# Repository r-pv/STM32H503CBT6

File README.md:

# STM32H503CBT6
ST development board based on the STM32H503CBT6 MCU. Compatible with Arduino.

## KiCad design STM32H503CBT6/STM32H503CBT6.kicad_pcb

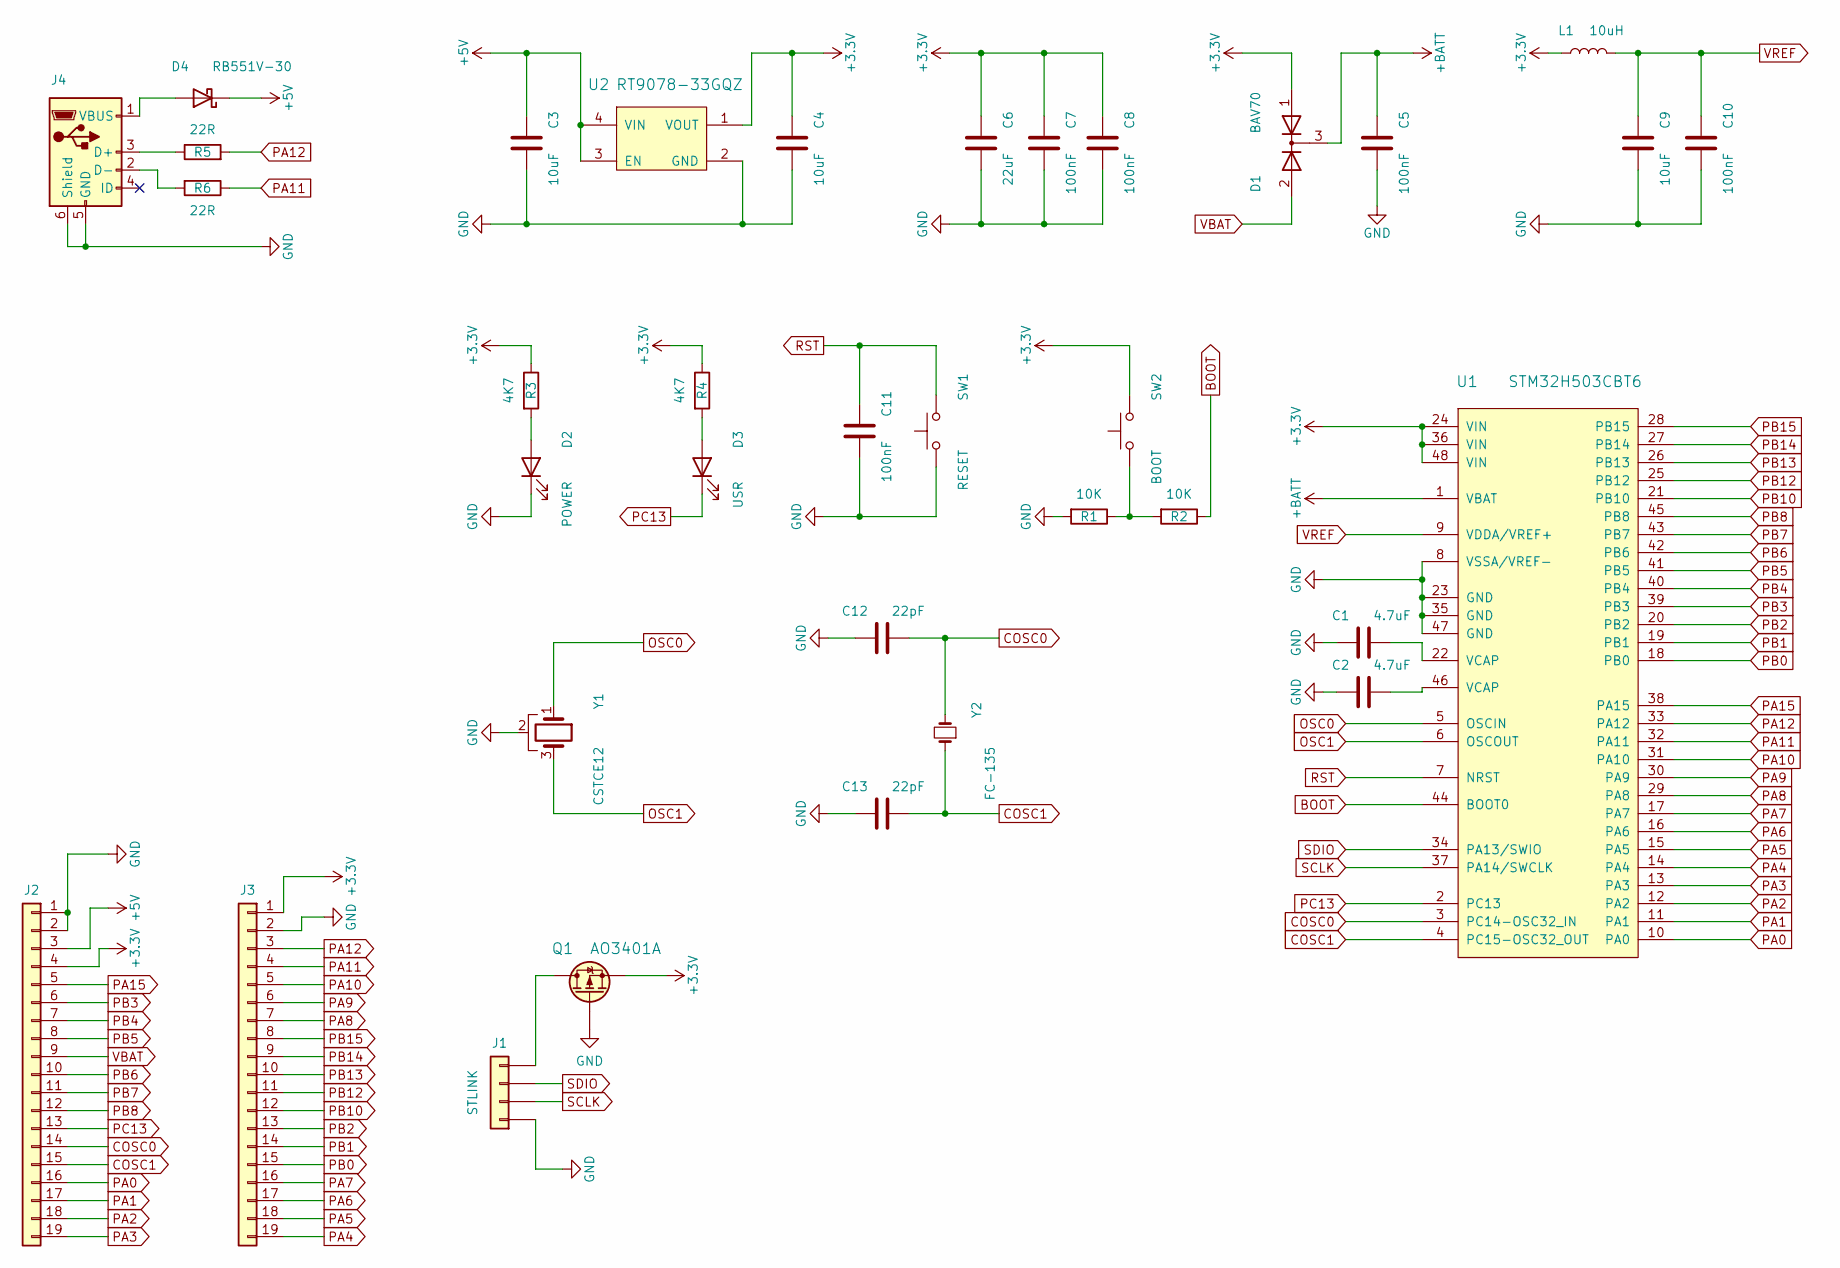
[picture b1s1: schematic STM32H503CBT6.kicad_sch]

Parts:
C1, C2: 4.7uF; C_0402_1005Metric
C3, C4, C9: 10uF; C_0402_1005Metric
C5, C7, C8, C10, C11: 100nF; C_0402_1005Metric
C6: 22uF; C_0805_2012Metric
C12, C13: 22pF; C_0402_1005Metric
D1: BAV70; SOT-23
D2: POWER; LED_0603_1608Metric
D3: USR; LED_0603_1608Metric
D4: RB551V-30; D_SOD-323
J1: STLINK; PinSocket_1x04_P2.54mm_Vertical
J2, J3: PinSocket_1x19_P2.54mm_Vertical
J4: connector_USB_Micro-B2
L1: 10uH; L_0603_1608Metric
Q1: AO3401A; SOT-23
R1, R2: 10K; R_0402_1005Metric
R3, R4: 4K7; R_0402_1005Metric
R5, R6: 22R; R_0402_1005Metric
SW1: RESET; Switch_SMD_5.2x6.4_reset
SW2: BOOT; Switch_SMD_5.2x6.4_reset
U1: STM32H503CBT6; LQFP-48_7x7mm_P0.5mm
U2: RT9078-33GQZ; XDFN4_1x1mm_0.65P
Y1: CSTCE12; Crystal_CSTCE_3pin_3.2x1.3
Y2: FC-135; Crystal_FC-135

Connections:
+3.3V: C4.1, C6.1, C7.1, C8.1, D1.1 (A), J2.4, J3.1, L1.1, Q1.2 (S), R3.1, R4.1, SW2.2, U1.24 (VIN), U1.36 (VIN), U1.48 (VIN), U2.1 (VOUT)
+5V: C3.1, D4.1 (K), J2.3, U2.3 (EN), U2.4 (VIN)
+BATT: C5.1, D1.3 (K), U1.1 (VBAT)
BOOT: R2.1, U1.44 (BOOT0)
COSC0: C12.2, J2.14, U1.3 (PC14-OSC32_IN), Y2.2
COSC1: C13.2, J2.15, U1.4 (PC15-OSC32_OUT), Y2.1
GND: C1.1, C2.1, C3.2, C4.2, C5.2, C6.2, C7.2, C8.2, C9.2, C10.2, C11.2, C12.1, C13.1, D2.1 (K), J1.1, J2.1, J2.2, J3.2, J4.5 (GND), J4.6 (Shield), Q1.1 (G), R1.2, SW1.1, U1.8 (VSSA/VREF-), U1.23 (GND), U1.35 (GND), U1.47 (GND), U2.2 (GND), Y1.2
unnamed: C1.2, U1.22 (VCAP)
unnamed: C2.2, U1.46 (VCAP)
unnamed: D2.2 (A), R3.2
unnamed: D3.2 (A), R4.2
unnamed: D4.2 (A), J4.1 (VBUS)
unnamed: J1.4, Q1.3 (D)
unnamed: J4.3 (D+), R5.1
unnamed: J4.2 (D-), R6.2
unnamed: R1.1, R2.2, SW2.1
OSC0: U1.5 (OSCIN), Y1.1
OSC1: U1.6 (OSCOUT), Y1.3
PA0: J2.16, U1.10 (PA0)
PA1: J2.17, U1.11 (PA1)
PA2: J2.18, U1.12 (PA2)
PA3: J2.19, U1.13 (PA3)
PA4: J3.19, U1.14 (PA4)
PA5: J3.18, U1.15 (PA5)
PA6: J3.17, U1.16 (PA6)
PA7: J3.16, U1.17 (PA7)
PA8: J3.7, U1.29 (PA8)
PA9: J3.6, U1.30 (PA9)
PA10: J3.5, U1.31 (PA10)
PA11: J3.4, R6.1, U1.32 (PA11)
PA12: J3.3, R5.2, U1.33 (PA12)
PA15: J2.5, U1.38 (PA15)
PB0: J3.15, U1.18 (PB0)
PB1: J3.14, U1.19 (PB1)
PB2: J3.13, U1.20 (PB2)
PB3: J2.6, U1.39 (PB3)
PB4: J2.7, U1.40 (PB4)
PB5: J2.8, U1.41 (PB5)
PB6: J2.10, U1.42 (PB6)
PB7: J2.11, U1.43 (PB7)
PB8: J2.12, U1.45 (PB8)
PB10: J3.12, U1.21 (PB10)
PB12: J3.11, U1.25 (PB12)
PB13: J3.10, U1.26 (PB13)
PB14: J3.9, U1.27 (PB14)
PB15: J3.8, U1.28 (PB15)
PC13: D3.1 (K), J2.13, U1.2 (PC13)
RST: C11.1, SW1.2, U1.7 (NRST)
SCLK: J1.2, U1.37 (PA14/SWCLK)
SDIO: J1.3, U1.34 (PA13/SWIO)
VBAT: D1.2 (A), J2.9
VREF: C9.1, C10.1, L1.2, U1.9 (VDDA/VREF+)

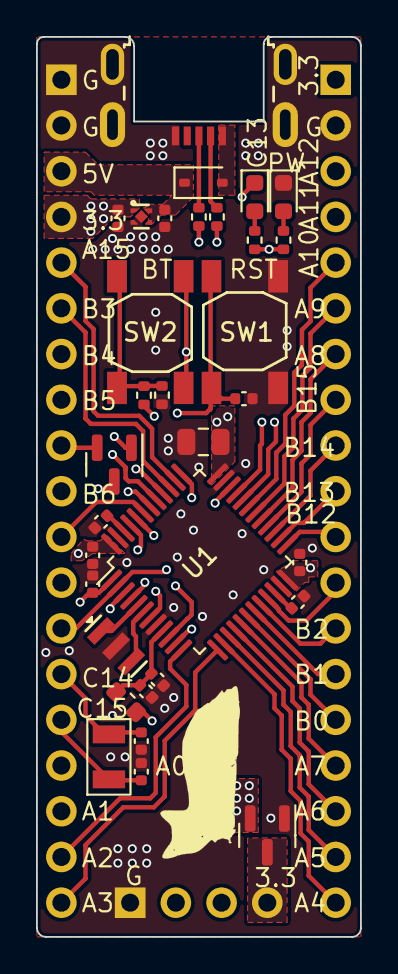
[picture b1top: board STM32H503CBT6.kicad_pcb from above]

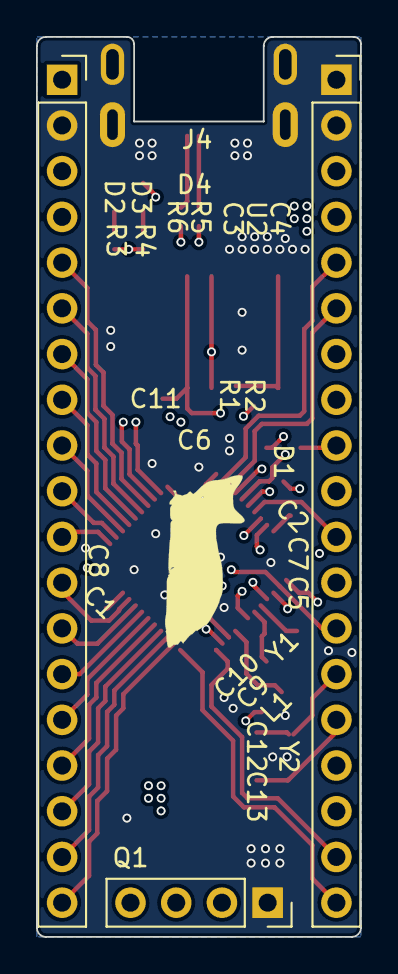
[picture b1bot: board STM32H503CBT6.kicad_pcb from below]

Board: 4 copper layers, 18.0 x 50.0 mm, 35 parts (3 on the bottom side), 52 nets.

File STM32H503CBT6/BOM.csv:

"Reference","Value","Footprint","Datasheet","Qty"
"C1, C2","4.7uF","Capacitor_SMD:C_0402_1005Metric","~","2"
"C3, C4, C9","10uF","Capacitor_SMD:C_0402_1005Metric","~","3"
"C5, C7, C8, C10, C11","100nF","Capacitor_SMD:C_0402_1005Metric","~","5"
"C6","22uF","Capacitor_SMD:C_0805_2012Metric","~","1"
"C12, C13","22pF","Capacitor_SMD:C_0402_1005Metric","~","2"
"D1","BAV70","Package_TO_SOT_SMD:SOT-23","https://assets.nexperia.com/documents/data-sheet/BAV70_SER.pdf","1"
"D2","POWER","LED_SMD:LED_0603_1608Metric","~","1"
"D3","USR","LED_SMD:LED_0603_1608Metric","~","1"
"D4","RB551V-30","Diode_SMD:D_SOD-323","~","1"
"J1","STLINK","Connector_PinSocket_2.54mm:PinSocket_1x04_P2.54mm_Vertical","~","1"
"J2, J3"," ","Connector_PinSocket_2.54mm:PinSocket_1x19_P2.54mm_Vertical","~","2"
"J4"," ","connector_USB_Micro-B2","~","1"
"L1","10uH","Inductor_SMD:L_0603_1608Metric","~","1"
"Q1","AO3401A","Package_TO_SOT_SMD:SOT-23","","1"
"R1, R2","10K","Resistor_SMD:R_0402_1005Metric","~","2"
"R3, R4","4K7","Resistor_SMD:R_0402_1005Metric","~","2"
"R5, R6","22R","Resistor_SMD:R_0402_1005Metric","~","2"
"SW1","RESET","Switch_SMD_5.2x6.4_reset","~","1"
"SW2","BOOT","Switch_SMD_5.2x6.4_reset","~","1"
"U1","STM32H503CBT6","Package_QFP:LQFP-48_7x7mm_P0.5mm","","1"
"U2","RT9078-33GQZ","XDFN4_1x1mm_0.65P","","1"
"Y1","CSTCE12","Crystal_CSTCE_3pin_3.2x1.3","~","1"
"Y2","FC-135


","Crystal_FC-135","~","1"

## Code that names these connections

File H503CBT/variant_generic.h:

/*
 *******************************************************************************
 * Copyright (c) 2020, STMicroelectronics
 * All rights reserved.
 *
 * This software component is licensed by ST under BSD 3-Clause license,
 * the "License"; You may not use this file except in compliance with the
 * License. You may obtain a copy of the License at:
 *                        opensource.org/licenses/BSD-3-Clause
 *
 *******************************************************************************
 */
#pragma once

/*----------------------------------------------------------------------------
 *        STM32 pins number
 *----------------------------------------------------------------------------*/
#define PA0                     PIN_A0
#define PA1                     PIN_A1
#define PA2                     PIN_A2
#define PA3                     PIN_A3
#define PA4                     PIN_A4
#define PA5                     PIN_A5
#define PA6                     PIN_A6
#define PA7                     PIN_A7
#define PA8                     8
#define PA9                     9
#define PA10                    10
#define PA11                    11
#define PA12                    12
#define PA13                    13
#define PA14                    14
#define PA15                    15
#define PB0                     PIN_A8
#define PB1                     PIN_A9
#define PB2                     18
#define PB3                     19
#define PB4                     20
#define PB5                     21
#define PB6                     22
#define PB7                     23
#define PB8                     24
#define PB10                    25
#define PB12                    26
#define PB13                    27
#define PB14                    28
#define PB15                    29
#define PC13                    30
#define PC14                    31
#define PC15                    32
#define PH0                     33
#define PH1                     34

// Alternate pins number
#define PA0_ALT1                (PA0  | ALT1)
#define PA0_ALT2                (PA0  | ALT2)
#define PA1_ALT1                (PA1  | ALT1)
#define PA2_ALT1                (PA2  | ALT1)
#define PA3_ALT1                (PA3  | ALT1)
#define PA4_ALT1                (PA4  | ALT1)
#define PA5_ALT1                (PA5  | ALT1)
#define PA7_ALT1                (PA7  | ALT1)
#define PA7_ALT2                (PA7  | ALT2)
#define PA8_ALT1                (PA8  | ALT1)
#define PA8_ALT2                (PA8  | ALT2)
#define PA9_ALT1                (PA9  | ALT1)
#define PA10_ALT1               (PA10 | ALT1)
#define PA11_ALT1               (PA11 | ALT1)
#define PA12_ALT1               (PA12 | ALT1)
#define PA13_ALT1               (PA13 | ALT1)
#define PA14_ALT1               (PA14 | ALT1)
#define PA14_ALT2               (PA14 | ALT2)
#define PA15_ALT1               (PA15 | ALT1)
#define PB0_ALT1                (PB0  | ALT1)
#define PB1_ALT1                (PB1  | ALT1)
#define PB1_ALT2                (PB1  | ALT2)
#define PB2_ALT1                (PB2  | ALT1)
#define PB3_ALT1                (PB3  | ALT1)
#define PB4_ALT1                (PB4  | ALT1)
#define PB4_ALT2                (PB4  | ALT2)
#define PB5_ALT1                (PB5  | ALT1)
#define PB6_ALT1                (PB6  | ALT1)
#define PB6_ALT2                (PB6  | ALT2)
#define PB7_ALT1                (PB7  | ALT1)
#define PB13_ALT1               (PB13 | ALT1)
#define PB14_ALT1               (PB14 | ALT1)
#define PB15_ALT1               (PB15 | ALT1)
#define PB15_ALT2               (PB15 | ALT2)

#define NUM_DIGITAL_PINS        35
#define NUM_ANALOG_INPUTS       10

// On-board LED pin number
#ifndef LED_BUILTIN
  #define LED_BUILTIN           PC13
#endif

// On-board user button
#ifndef USER_BTN
  #define USER_BTN              PNUM_NOT_DEFINED
#endif

// SPI definitions
#ifndef PIN_SPI_SS
  #define PIN_SPI_SS            PA4
#endif
#ifndef PIN_SPI_SS1
  #define PIN_SPI_SS1           PA4_ALT1
#endif
#ifndef PIN_SPI_SS2
  #define PIN_SPI_SS2           PA15_ALT1
#endif
#ifndef PIN_SPI_SS3
  #define PIN_SPI_SS3           PB10
#endif
#ifndef PIN_SPI_MOSI
  #define PIN_SPI_MOSI          PA7
#endif
#ifndef PIN_SPI_MISO
  #define PIN_SPI_MISO          PA6
#endif
#ifndef PIN_SPI_SCK
  #define PIN_SPI_SCK           PA5
#endif

// I2C definitions
#ifndef PIN_WIRE_SDA
  #define PIN_WIRE_SDA          PB7
#endif
#ifndef PIN_WIRE_SCL
  #define PIN_WIRE_SCL          PB6
#endif

// Timer Definitions
// Use TIM6/TIM7 when possible as servo and tone don't need GPIO output pin
#ifndef TIMER_TONE
  #define TIMER_TONE            TIM6
#endif
#ifndef TIMER_SERVO
  #define TIMER_SERVO           TIM7
#endif

// UART Definitions
#ifndef SERIAL_UART_INSTANCE
  #define SERIAL_UART_INSTANCE  1
#endif

// Default pin used for generic 'Serial' instance
// Mandatory for Firmata
#ifndef PIN_SERIAL_RX
  #define PIN_SERIAL_RX         PA10
#endif
#ifndef PIN_SERIAL_TX
  #define PIN_SERIAL_TX         PA9
#endif


#define HSE_VALUE               12000000UL /*!< Value of the External oscillator in Hz */


// Extra HAL modules
#if !defined(HAL_DAC_MODULE_DISABLED)
  #define HAL_DAC_MODULE_ENABLED
#endif

/*----------------------------------------------------------------------------
 *        Arduino objects - C++ only
 *----------------------------------------------------------------------------*/

#ifdef __cplusplus
  // These serial port names are intended to allow libraries and architecture-neutral
  // sketches to automatically default to the correct port name for a particular type
  // of use.  For example, a GPS module would normally connect to SERIAL_PORT_HARDWARE_OPEN,
  // the first hardware serial port whose RX/TX pins are not dedicated to another use.
  //
  // SERIAL_PORT_MONITOR        Port which normally prints to the Arduino Serial Monitor
  //
  // SERIAL_PORT_USBVIRTUAL     Port which is USB virtual serial
  //
  // SERIAL_PORT_LINUXBRIDGE    Port which connects to a Linux system via Bridge library
  //
  // SERIAL_PORT_HARDWARE       Hardware serial port, physical RX & TX pins.
  //
  // SERIAL_PORT_HARDWARE_OPEN  Hardware serial ports which are open for use.  Their RX & TX
  //                            pins are NOT connected to anything by default.
  #ifndef SERIAL_PORT_MONITOR
    #define SERIAL_PORT_MONITOR   Serial
  #endif
  #ifndef SERIAL_PORT_HARDWARE
    #define SERIAL_PORT_HARDWARE  Serial
  #endif
#endif

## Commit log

2024-02-01 KiCAD Files.
    Board Files.
2024-02-01 Arduino Variant
    Pending...
2024-09-06 Delete H503CBT/H503CB(T-U)_000.rar
    original variant from the STcore
